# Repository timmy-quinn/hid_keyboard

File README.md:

# The KeyBird
The KeyBird is a BLE split keyboard with a vertical stagger and 5 thumb keys. It features hot-swap sockets compatible with any MX switches. The design is inspired by other popular split keyboards such as the [Corne](https://github.com/foostan/crkbd) or [Kinesis keyboards](https://kinesis-ergo.com/?gad_source=1&gclid=CjwKCAiAwaG9BhAREiwAdhv6Y5c0aeCQfguv5zLsIx9gEMnvGuGCnlFAN4PNxmo4kbpMpXuSq_xYTRoC38cQAvD_BwE).

## Project Status
### Firmware 
- [x] Proof of concept: Single board BLE HID over GATT
- [x] Key matrix
- [x] Multi-role functionality
- [x] Process keypresses from secondary keyboard
- [ ] Improvements based on user experience
### Electronics 
- [x] Proof of concept: Perf board
- [x] Design and order PCBs
- [x] Assemble PCBs
- [ ] Improvements based on user experience 
### Case
- [x] Design case and plate
- [ ] 3D-print case and plate
- [ ] Build a wooden case
### Stretch goals
- [ ] Enable tenting
- [ ] Add NFC pairing capability
- [ ] Add USB option
- [ ] Add RGB LEDs
- [ ] OTA update
- [ ] Keyboard configuration via file upload

### Design Notes (AKA why does it look like that?) 
If you've never plunged down the ergonomic keyboard rabbit hole before, I'll give you a quick breakdown explaining some of the design decisions that went into my keyboard.  
  
**1. Split**  
Splitting a keyboard in half allows your hands and wrists to rest at a more natural and comfortable position  
**2. Ortholinear**   
This is just a fancy way to say that the keys are layed out in vertical columns, unlike typical keyboards, where the keys form horizontal rows, but are vertically staggered. Using vertical columns, especially when those columns are staggered to conform with the length of each finger, provides a more ergnomic typing experience.
**3. Reduced key count**  
Reducing the number of keys enables you to type faster and more efficiently since you do not have to stretch your fingers for hard to reach keys. This is especially helpful for coding, where you have to use symbols like ~ and | more often than most typers. But you might wonder, if you reduce the number of keys, don't you reduct the number of characters you can type? That is where the next design principle comes into play.
**4. Layers**  
A reduced keyboard makes up for its lack of keys by using layers. Layers are changed with the press of a button. When pressing the layer button, the same physical keys will transmit a different character to your PC. The shift key on a normal keyboard functions like this. On a reduced size keyboard, there will be at least one other layer key besides the shift key, enabling the same number of characters to be typed with fewer keys.  
**5. Thumb cluster**  
The thumb cluster solves one of the inefficiences of a standard keyboard, where both of your thumbs are dedicated to a single key. Adding a thumb cluster enables you to press far more keys without increasing how much you have to move your hand. This helps counter balance the reduced key size, while still preventing you from have to stretch and reach to use necessary keys.  
  
## Development requirements  
For hardware development KiCad 8 is used. 

For firmware Development nRF Connect SDK v2.6.1 is required. It can be conveniently used with the NRF Visual Studio Code Extension. More information can be found [here](https://docs.nordicsemi.com/bundle/ncs-latest/page/nrf/installation/install_ncs.html). 

#### Generating first build.  
1. Navigate to the NRF Connect Tab in VS Code.  

2. Select Add Build Configuration.  

3. Choose one of the presets. The presets are determined by the CMakePresets.json, but they can be simply be selected in the GUI.

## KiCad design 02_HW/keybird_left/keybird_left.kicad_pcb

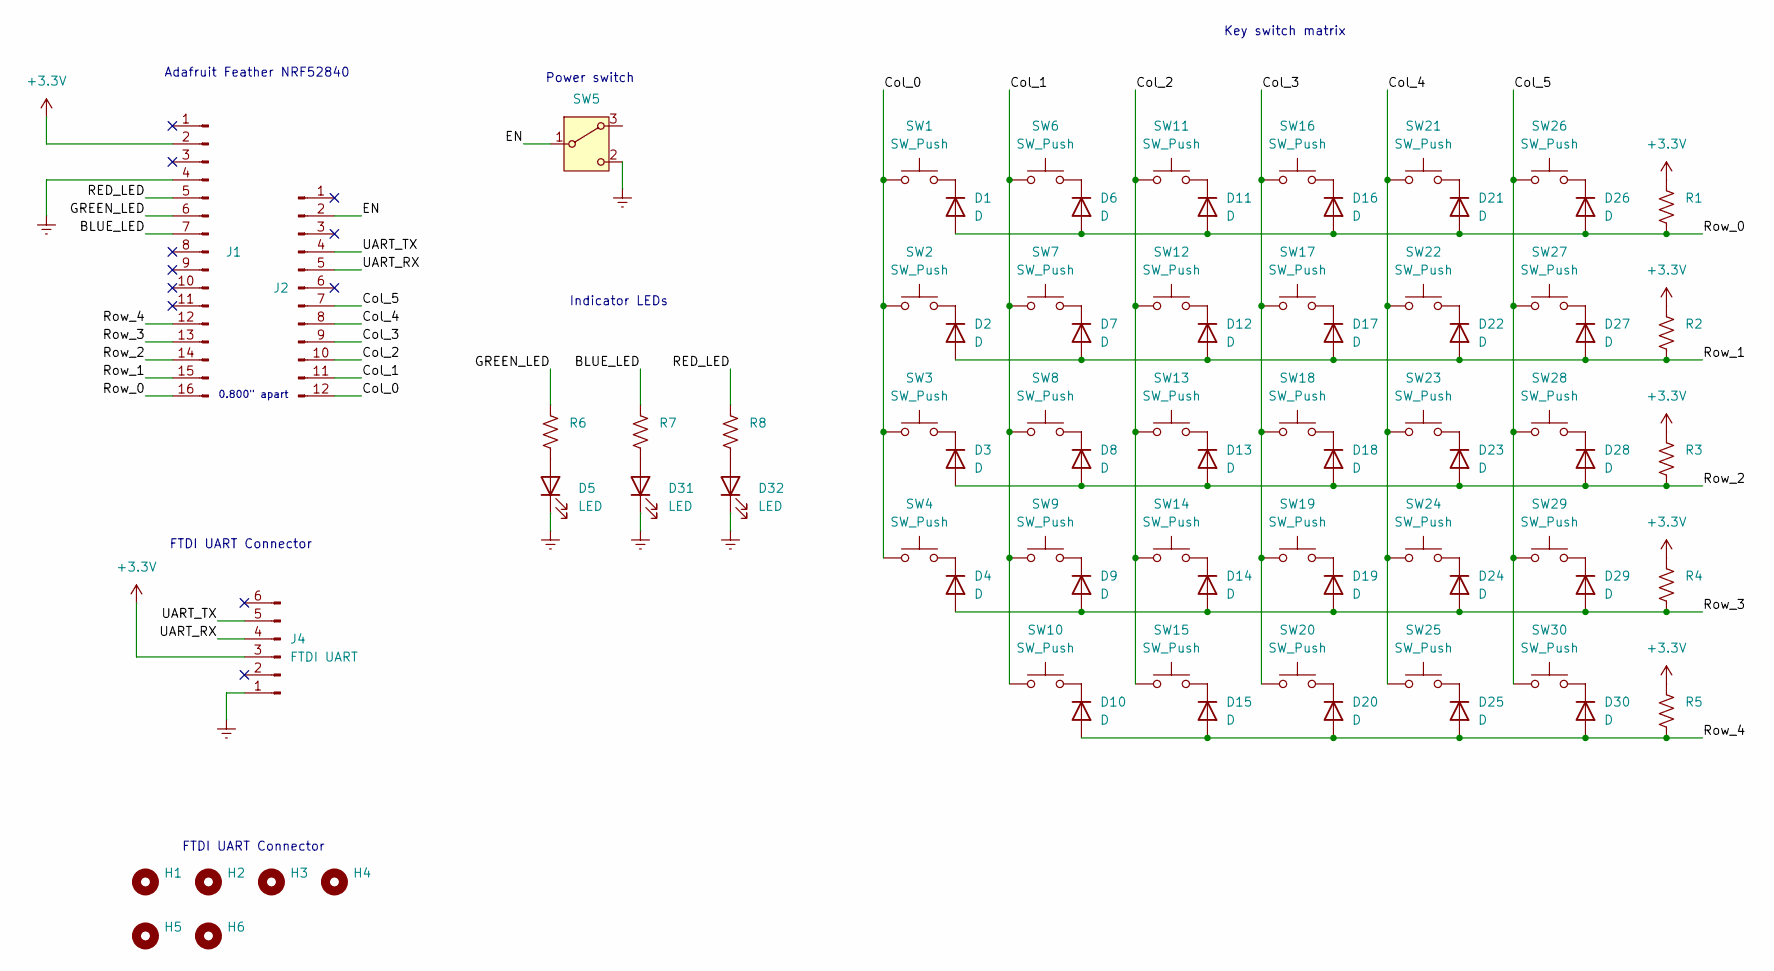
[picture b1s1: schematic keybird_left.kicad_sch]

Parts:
D1, D2, D3, D4, D6, D7, D8, D9, D10, D11, D12, D13, D14, D15, D16, D17, D18, D19, D20, D21, D22, D23, D24, D25, D26, D27, D28, D29, D30: D; Nexperia_CFP3_SOD-123W
D5, D31, D32: LED; LED_0603_1608Metric
H1, H2, H3, H4, H5, H6: MountingHole; MountingHole_2.5mm
J1: Adafruit_Feather_16_pin; PinSocket_1x16_P2.54mm_Vertical
J2: Adafruit_feather_12_pin; PinSocket_1x12_P2.54mm_Vertical
J4: FTDI UART; PinHeader_1x06_P2.54mm_Vertical
R1, R2, R3, R4, R5, R6, R7, R8: R_US; R_0603_1608Metric
SW1, SW2, SW3, SW4, SW6, SW7, SW8, SW9, SW10, SW11, SW12, SW13, SW14, SW15, SW16, SW17, SW18, SW19, SW20, SW21, SW22, SW23, SW24, SW25, SW26, SW27, SW28, SW29, SW30: SW_Push; SW_Hotswap_Kailh_MX_1.00u
SW5: Power enable; SW_Slide-03_Wuerth-WS-SLTV_10x2.5x6.4_P2.54mm

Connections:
+3.3V: J1.2, J4.3, R1.1, R2.1, R3.1, R4.1, R5.1
/BLUE_LED: J1.7, R7.1
/Col_0: J2.12, SW1.1, SW2.1, SW3.1, SW4.1
/Col_1: J2.11, SW6.1, SW7.1, SW8.1, SW9.1, SW10.1
/Col_2: J2.10, SW11.1, SW12.1, SW13.1, SW14.1, SW15.1
/Col_3: J2.9, SW16.1, SW17.1, SW18.1, SW19.1, SW20.1
/Col_4: J2.8, SW21.1, SW22.1, SW23.1, SW24.1, SW25.1
/Col_5: J2.7, SW26.1, SW27.1, SW28.1, SW29.1, SW30.1
/EN: J2.2, SW5.1 (B)
/GREEN_LED: J1.6, R6.1
/RED_LED: J1.5, R8.1
/Row_0: D1.2 (A), D6.2 (A), D11.2 (A), D16.2 (A), D21.2 (A), D26.2 (A), J1.16, R1.2
/Row_1: D2.2 (A), D7.2 (A), D12.2 (A), D17.2 (A), D22.2 (A), D27.2 (A), J1.15, R2.2
/Row_2: D3.2 (A), D8.2 (A), D13.2 (A), D18.2 (A), D23.2 (A), D28.2 (A), J1.14, R3.2
/Row_3: D4.2 (A), D9.2 (A), D14.2 (A), D19.2 (A), D24.2 (A), D29.2 (A), J1.13, R4.2
/Row_4: D10.2 (A), D15.2 (A), D20.2 (A), D25.2 (A), D30.2 (A), J1.12, R5.2
/UART_RX: J2.5, J4.4
/UART_TX: J2.4, J4.5
GNDREF: D5.1 (K), D31.1 (K), D32.1 (K), J1.4, J4.1, SW5.2 (C)
unnamed: D1.1 (K), SW1.2
unnamed: D2.1 (K), SW2.2
unnamed: D3.1 (K), SW3.2
unnamed: D4.1 (K), SW4.2
unnamed: D5.2 (A), R6.2
unnamed: D6.1 (K), SW6.2
unnamed: D7.1 (K), SW7.2
unnamed: D8.1 (K), SW8.2
unnamed: D9.1 (K), SW9.2
unnamed: D10.1 (K), SW10.2
unnamed: D11.1 (K), SW11.2
unnamed: D12.1 (K), SW12.2
unnamed: D13.1 (K), SW13.2
unnamed: D14.1 (K), SW14.2
unnamed: D15.1 (K), SW15.2
unnamed: D16.1 (K), SW16.2
unnamed: D17.1 (K), SW17.2
unnamed: D18.1 (K), SW18.2
unnamed: D19.1 (K), SW19.2
unnamed: D20.1 (K), SW20.2
unnamed: D21.1 (K), SW21.2
unnamed: D22.1 (K), SW22.2
unnamed: D23.1 (K), SW23.2
unnamed: D24.1 (K), SW24.2
unnamed: D25.1 (K), SW25.2
unnamed: D26.1 (K), SW26.2
unnamed: D27.1 (K), SW27.2
unnamed: D28.1 (K), SW28.2
unnamed: D29.1 (K), SW29.2
unnamed: D30.1 (K), SW30.2
unnamed: D31.2 (A), R7.2
unnamed: D32.2 (A), R8.2

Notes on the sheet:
FTDI UART Connector
0.800" apart
Power switch
Adafruit Feather NRF52840
Indicator LEDs
Key switch matrix

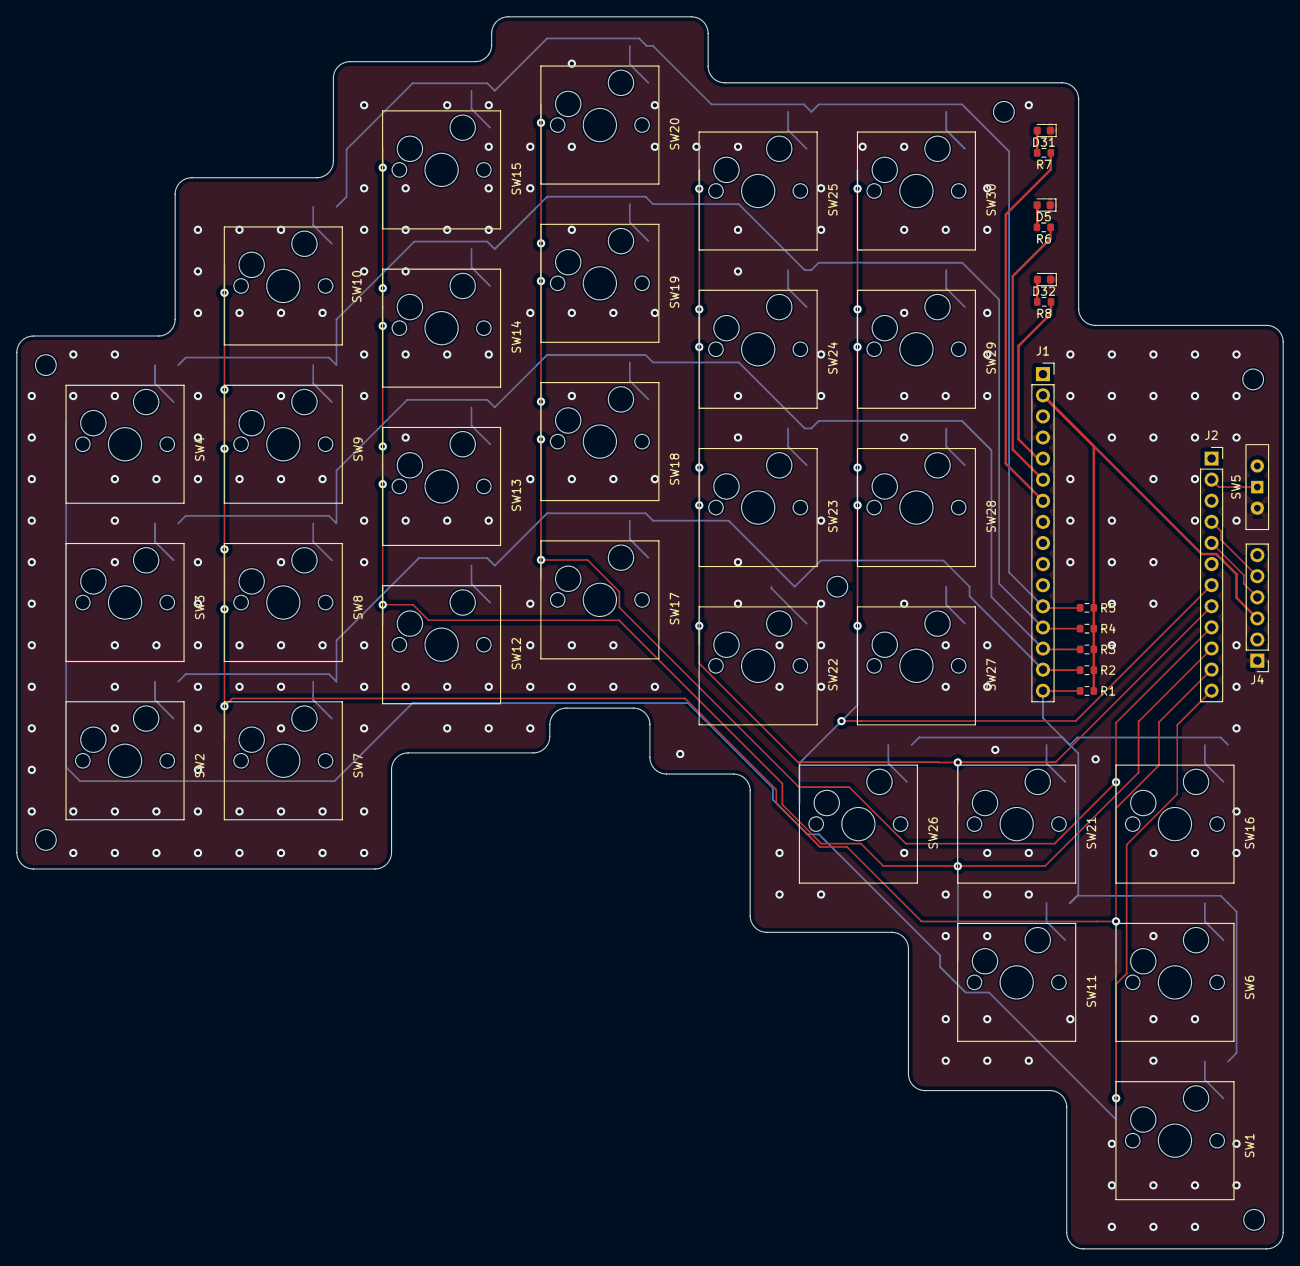
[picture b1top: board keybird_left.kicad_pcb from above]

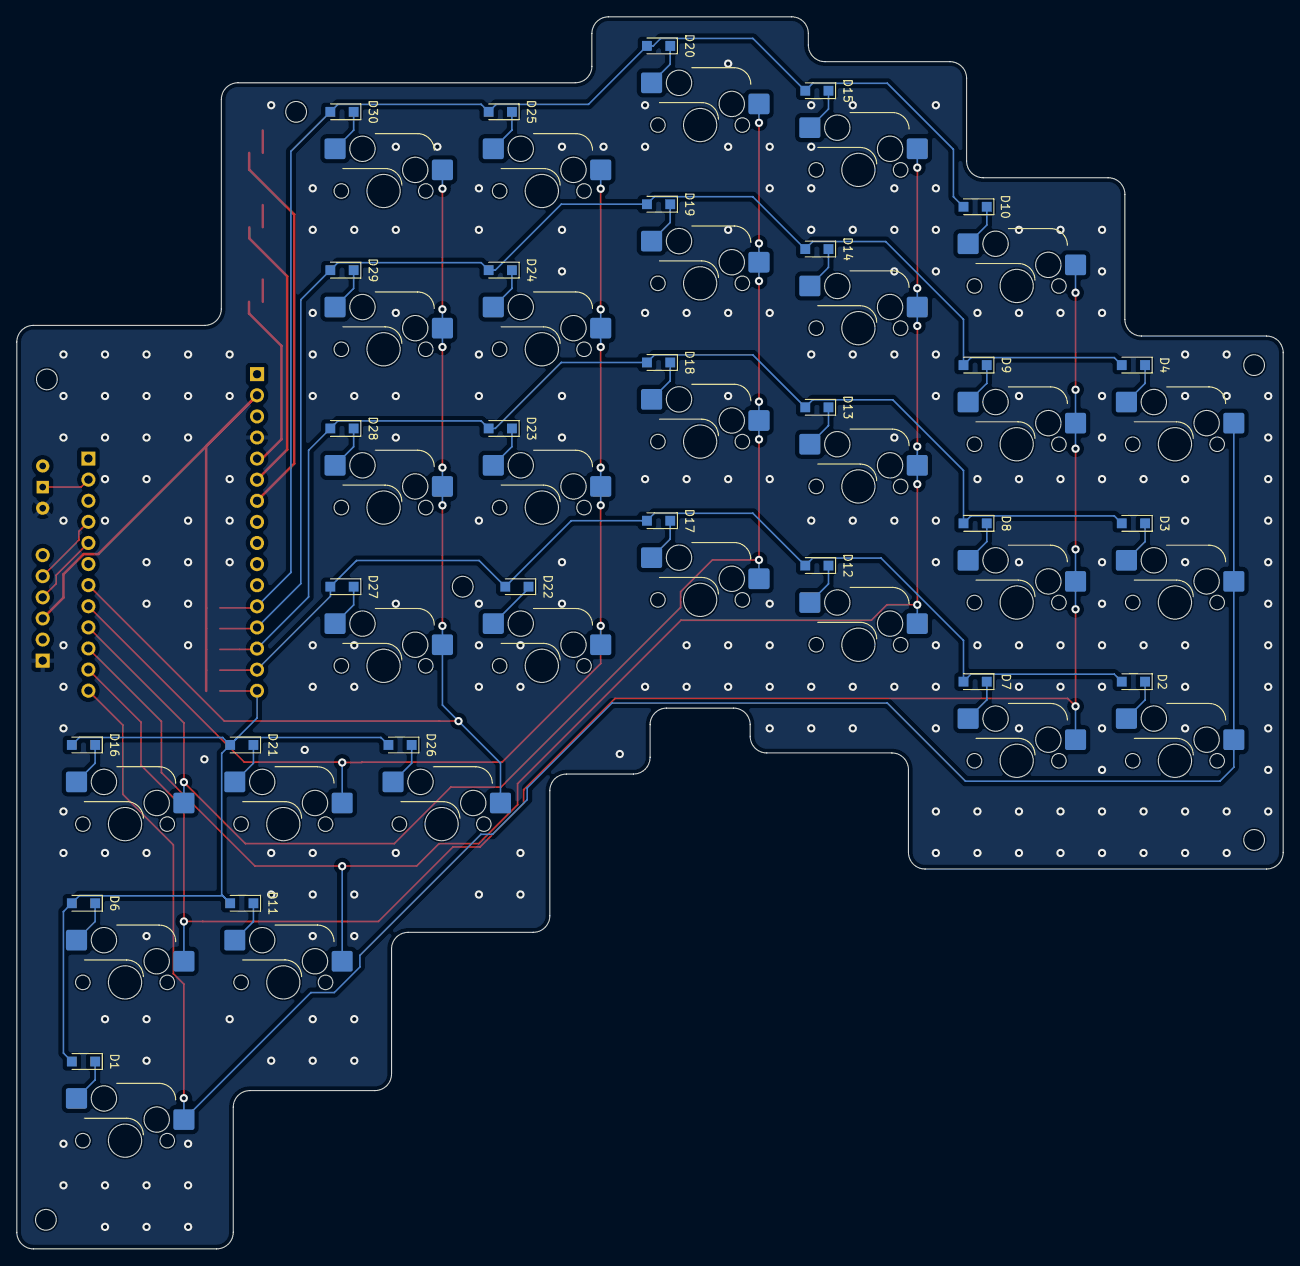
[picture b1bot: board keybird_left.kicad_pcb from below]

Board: 2 copper layers, 152.4 x 148.3 mm, 79 parts (29 on the bottom side), 51 nets.

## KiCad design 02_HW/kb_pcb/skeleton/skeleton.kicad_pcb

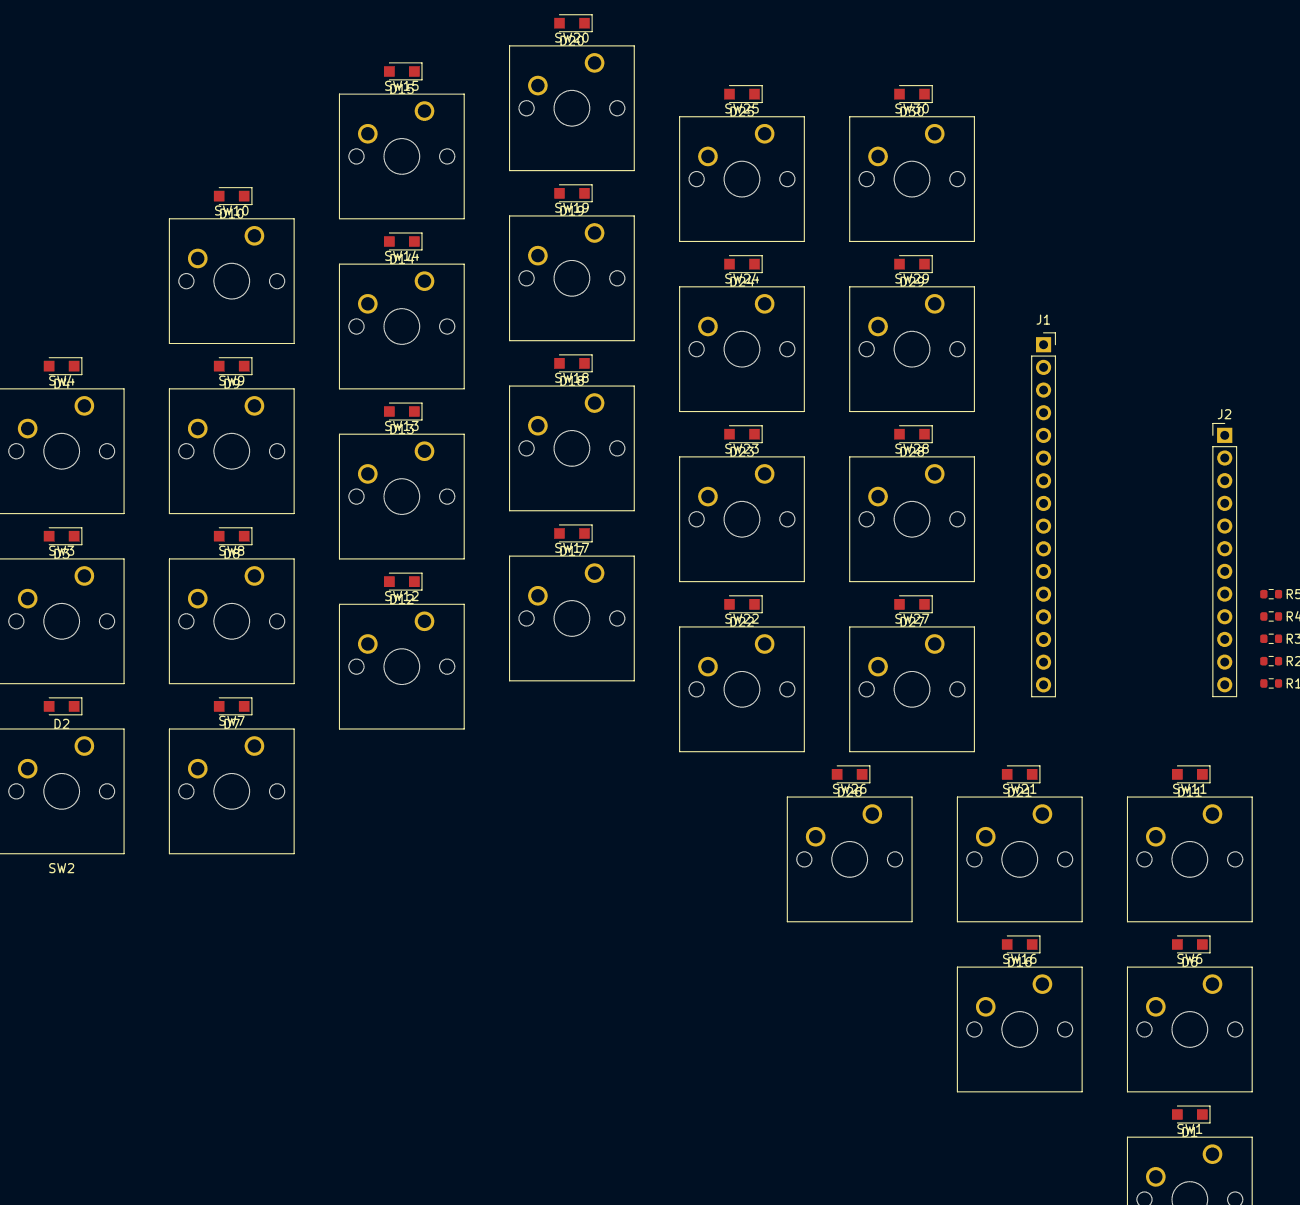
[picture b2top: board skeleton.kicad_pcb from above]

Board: 2 copper layers, 65 parts (0 on the bottom side), 41 nets, no tracks yet.

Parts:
D1, D2, D3, D4, D6, D7, D8, D9, D10, D11, D12, D13, D14, D15, D16, D17, D18, D19, D20, D21, D22, D23, D24, D25, D26, D27, D28, D29, D30: D; Nexperia_CFP3_SOD-123W
J1: Adafruit_Feather_16_pin; PinSocket_1x16_P2.54mm_Vertical
J2: Adafruit_feather_12_pin; PinHeader_1x12_P2.54mm_Vertical
R1, R2, R3, R4, R5: R_US; R_0603_1608Metric
SW1, SW2, SW3, SW4, SW6, SW7, SW8, SW9, SW10, SW11, SW12, SW13, SW14, SW15, SW16, SW17, SW18, SW19, SW20, SW21, SW22, SW23, SW24, SW25, SW26, SW27, SW28, SW29, SW30: SW_Push; SW_Cherry_MX_1.00u_PCB

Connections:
+3.3V: R1.1, R2.1, R3.1, R4.1, R5.1
/Col_0: J1.6, SW1.1, SW2.1, SW3.1, SW4.1
/Col_1: J1.7, SW6.1, SW7.1, SW8.1, SW9.1, SW10.1
/Col_2: J1.8, SW11.1, SW12.1, SW13.1, SW14.1, SW15.1
/Col_3: J1.9, SW16.1, SW17.1, SW18.1, SW19.1, SW20.1
/Col_4: J1.10, SW21.1, SW22.1, SW23.1, SW24.1, SW25.1
/Col_5: J1.11, SW26.1, SW27.1, SW28.1, SW29.1, SW30.1
/Row_0: D1.1 (K), D6.1 (K), D11.1 (K), D16.1 (K), D21.1 (K), D26.1 (K), J2.12, R1.2
/Row_1: D2.1 (K), D7.1 (K), D12.1 (K), D17.1 (K), D22.1 (K), D27.1 (K), J2.11, R2.2
/Row_2: D3.1 (K), D8.1 (K), D13.1 (K), D18.1 (K), D23.1 (K), D28.1 (K), J2.10, R3.2
/Row_3: D4.1 (K), D9.1 (K), D14.1 (K), D19.1 (K), D24.1 (K), D29.1 (K), J2.9, R4.2
/Row_4: D10.1 (K), D15.1 (K), D20.1 (K), D25.1 (K), D30.1 (K), J2.8, R5.2
unnamed: D1.2 (A), SW1.2
unnamed: D2.2 (A), SW2.2
unnamed: D3.2 (A), SW3.2
unnamed: D4.2 (A), SW4.2
unnamed: D6.2 (A), SW6.2
unnamed: D7.2 (A), SW7.2
unnamed: D8.2 (A), SW8.2
unnamed: D9.2 (A), SW9.2
unnamed: D10.2 (A), SW10.2
unnamed: D11.2 (A), SW11.2
unnamed: D12.2 (A), SW12.2
unnamed: D13.2 (A), SW13.2
unnamed: D14.2 (A), SW14.2
unnamed: D15.2 (A), SW15.2
unnamed: D16.2 (A), SW16.2
unnamed: D17.2 (A), SW17.2
unnamed: D18.2 (A), SW18.2
unnamed: D19.2 (A), SW19.2
unnamed: D20.2 (A), SW20.2
unnamed: D21.2 (A), SW21.2
unnamed: D22.2 (A), SW22.2
unnamed: D23.2 (A), SW23.2
unnamed: D24.2 (A), SW24.2
unnamed: D25.2 (A), SW25.2
unnamed: D26.2 (A), SW26.2
unnamed: D27.2 (A), SW27.2
unnamed: D28.2 (A), SW28.2
unnamed: D29.2 (A), SW29.2
unnamed: D30.2 (A), SW30.2

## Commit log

2024-10-20 Initial commit for peripheral_hids_keyboard
2024-10-21 vscode intellisense requirements
2024-10-22 Removed gpio functions
2024-10-22 removed includePath
2024-10-22 Added keys module
2024-11-04 added keys.c file
2024-11-05 Reorganized folder structure
2024-11-07 Added hid documentation
2024-11-07 Added basic gpio functions for a keyboard key matrix
2024-11-08 Added .vscode to .gitignore
2024-11-08 removed files in .vscode
2024-11-08 Adds compile export commands
2024-11-08 formatting
2024-11-10 implemented blink led test with device tree overlay
2024-11-13 Used overlay file for gpio scanning
2024-11-14 created key scan work item, began refactoring to snake_case
2024-11-14 Added README
2024-11-15 Key scan functions implemented via work queue
2024-11-15 Added scan codes
2024-11-15 bugfix - key scan functions, and all output pins set to high at the start
2024-11-16 Key scan function and hid implemented concurrently
2024-11-16 Sends keypresses from key matrix over gatt
2024-11-17 Beautified keys code
2024-11-17 Refactor
    Use kb_ naming convention for my files
    Move ble hid into its own file
    Delete unused code from main
2024-11-23 added overlay file
2024-11-23 Updated readme with NRF information
2024-11-23 deleted unnecessary readme
2024-11-24 Added PCB design files
2024-11-24 Added footprints
2024-11-26 Added header pins and diodes. Updated PCB from schematic
2024-11-27 Organized key layout
2024-11-27 Updated key placement
2024-11-29 Added adafruit board and board overlay
2024-12-01 Positioned key switches and diodes
2024-12-02 Positioned key switch columns. Began fixing net labels
2024-12-03 moved thumb pad, fixed net labels,added design rules
2024-12-03 Updated thumb pad layout, rearranged silkscreen
2024-12-05 Added key matrix device tree key binding and added to kb dts
2024-12-09 Updated board files to match prototype hardware
2024-12-09 Began implementing hid central feature
2024-12-12 Updated overlay to work with prototype board
2024-12-12 Changed name to KeyBird
2024-12-18 Implemented keyboard functionality for prototype board and printk funcitonality
2024-12-19 Added debug logs for testing, changed auth to just works
2025-01-05 added password authentication back
2025-01-08 clean up
2025-01-08 saved build configurations as a preset
2025-01-08 removed child_image build file
2025-01-12 Both BLE central and peripheral code implemented. (Not simultaneously)
2025-01-13 Peripheral and central functioning, but conflict with scanning and advertisiting. Also code is a complete mess
2025-01-14 Functions as relay. Cleaning up code
2025-01-14 cleans up further and refactoring
2025-01-15 Further cleanup
2025-01-17 Added queue to kb_central for passing information to keypress get thread
2025-01-19 Added photos of prototypes to README.md
2025-01-24 Debugging the btns send to work queue process
2025-01-25 Implements functional BLE relay
2025-01-27 bugfix: multi-key rollover with BLE relay
2025-01-28 bugfix: special buttons not working
2025-01-28 added .clang-format file
2025-01-28 reformatted source code files
2025-01-28 removed .vscode from main directory
2025-01-29 Reverseddiodes for active low implementation
2025-01-31 Added power switch and leds to pcb
2025-01-31 Updated uart connector to match ftdi cable pinout
2025-02-01 Added board outline
2025-02-05 Trimmed down board shape, completed tracing, adding ground pours and via stitching
2025-02-05 moved through holes in schematics
2025-02-08 Resolved design rule conflicts
2025-02-09 Finalizes left hand keyboard and creates template for right hand keyboard
2025-02-09 deleted old screenshot
2025-02-09 Renames right keyboard project file
2025-02-09 left and right board pass design rule checks
2025-02-09 renamed datasheet dir to notes
2025-02-09 Left and right boards pass design rule checks
2025-02-09 Created output files
2025-02-09 Zip output files
2025-02-09 Added screenshots of pcb files
2025-02-10 backups
2025-02-10 Deleted autosave file
2025-02-10 Moved photos into one folder
2025-02-10 Updated ReadMe with project status
2025-02-10 fixed path for README.md picture file
2025-02-10 Updated README
    Added Developement Requirements
2025-02-10 Added folder for mechanical parts (keyboard case)
2025-02-17 Added notes on keyboard case design
2025-02-17 Edited hardware files
2025-02-25 Ignore backup folders in kicad
2025-02-27 script can copy lines from footprints and paste them onto a new layer, however the positioning is off.
2025-03-03 Added note about switch cutout size
2025-03-09 added mechanical README
2025-03-09 added hw backups to .gitignore
2025-03-09 Moved button matrix configuration to overlay file
2025-03-22 Builds for both left and right hand keyboards
2025-03-22 Deletes commented out code
2025-03-22 Added photos and updated README.md
2025-03-22 Deleted unneeded files
2025-03-22 Removed unnecessary files
2025-03-22 Removed old backups
2025-03-23 Deletes old backups
2025-03-23 Removes unneeded files
2025-03-23 Removes redundant backups and files not needed in version control
2025-03-23 Add a few more scan codes
2025-03-23 Dev (#17)
    * Add a few more scan codes
    * Deleted unneeded files
2025-03-30 Adding neopixel support
2025-03-30 Added definitions for all scan codes
2025-03-30 Refactored scan code definitions
2025-03-30 Added complete set of scan codes (#18)
    * Defined scan codes for complete set of HID functionality.
    * Hijacked unused scan codes to enable additional functionality
2025-03-30 rename btns files to key_matrix files
